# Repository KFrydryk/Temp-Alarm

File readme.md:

# Temperature Sensor with timer and Alarm

It's a home project - gift for a girlfriend. The device can measure temperature using DS18B20 sensor on a probe, show real time measurements on LCD display and set off alarm when needed. It uses barebones Atmega328 chip powered by 3 AA batteries. It can work in 4 modes.

# Work Modes
Temp | Timer | Result
-------|-------|-------
Not Set | Not Set | Temperature is printed in real time, timer counts from 0 upwards, no alarm is set
Not Set | Set | Temperature is printed in real time, timer counts down to 0, alarm when timer reaches 0
Set | Not Set | Temperature is printed in real time, timer counts from 0 upwards, alarm is set off when set temperature is reached
Set | Set | Temperature is printed in real time, timer shows set value and starts counting down when set temp is reached. Alarm is set off whem timer reaches 0

# Schematics
All schematics should be uploaded in [Eagle_files folder](https://github.com/KFrydryk/Temp-Alarm/tree/master/Eagle_files)

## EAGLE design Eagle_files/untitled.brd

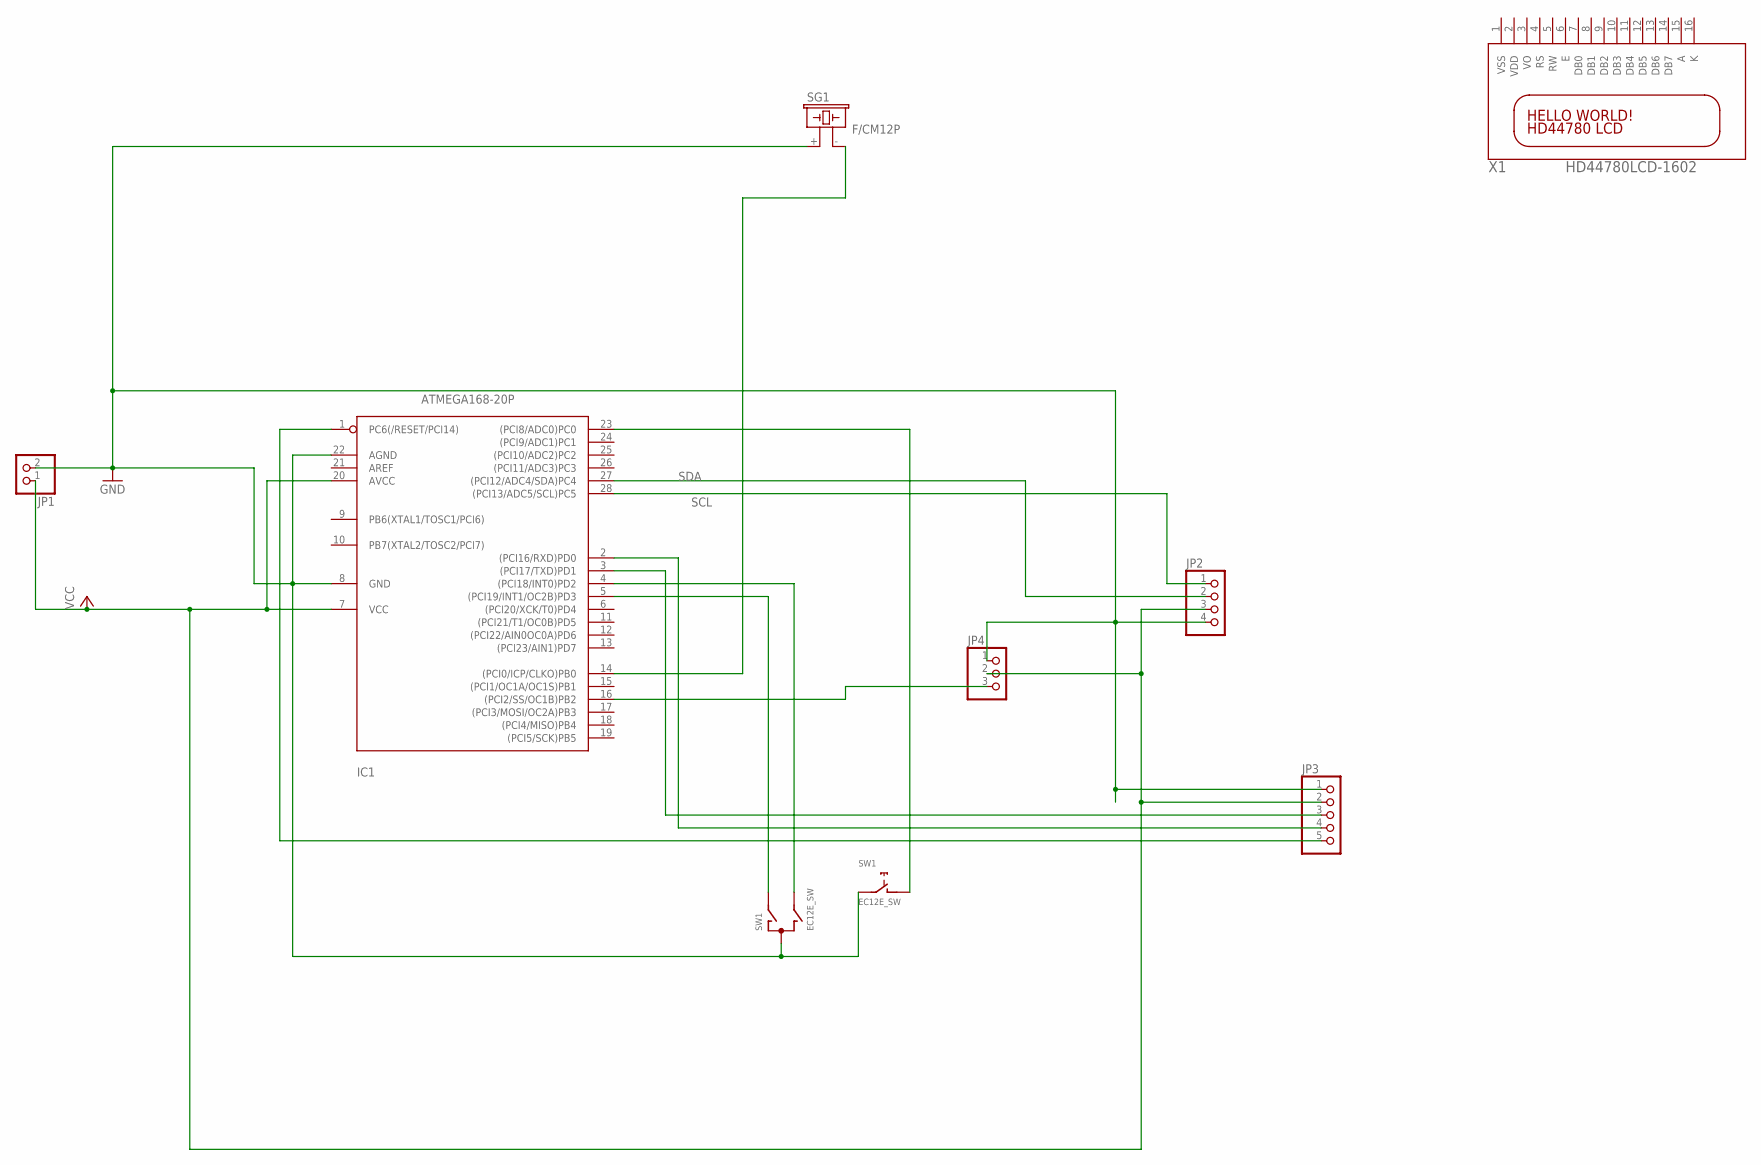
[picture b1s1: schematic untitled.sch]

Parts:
IC1: ATMEGA168-20P; DIL28-3
JP1: PINHD-1X2; 1X02
JP2: PINHD-1X4; 1X04
JP3: PINHD-1X5; 1X05
JP4: PINHD-1X3; 1X03
SG1: F/CM12P
SW1: EC12E_SW; ALPS_EC12E_SW
X1: HD44780LCD-1602; LCD1602

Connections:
GND: IC1.8 (GND), IC1.22 (AGND), JP1.2, JP2.4, JP3.1, JP4.1, SG1.+ (1), SW1.C, SW1.E (2)
unnamed: IC1.3 ((PCI17/TXD)PD1), JP3.3
unnamed: IC1.23 ((PCI8/ADC0)PC0), SW1.D (1)
unnamed: IC1.4 ((PCI18/INT0)PD2), SW1.B
unnamed: IC1.5 ((PCI19/INT1/OC2B)PD3), SW1.A
unnamed: IC1.2 ((PCI16/RXD)PD0), JP3.4
unnamed: IC1.14 ((PCI0/ICP/CLKO)PB0), SG1.- (2)
unnamed: IC1.1 (PC6(/RESET/PCI14)), JP3.5
unnamed: IC1.16 ((PCI2/SS/OC1B)PB2), JP4.3
SCL: IC1.28 ((PCI13/ADC5/SCL)PC5), JP2.1
SDA: IC1.27 ((PCI12/ADC4/SDA)PC4), JP2.2
VCC: IC1.7 (VCC), IC1.20 (AVCC), JP1.1, JP2.3, JP3.2, JP4.2

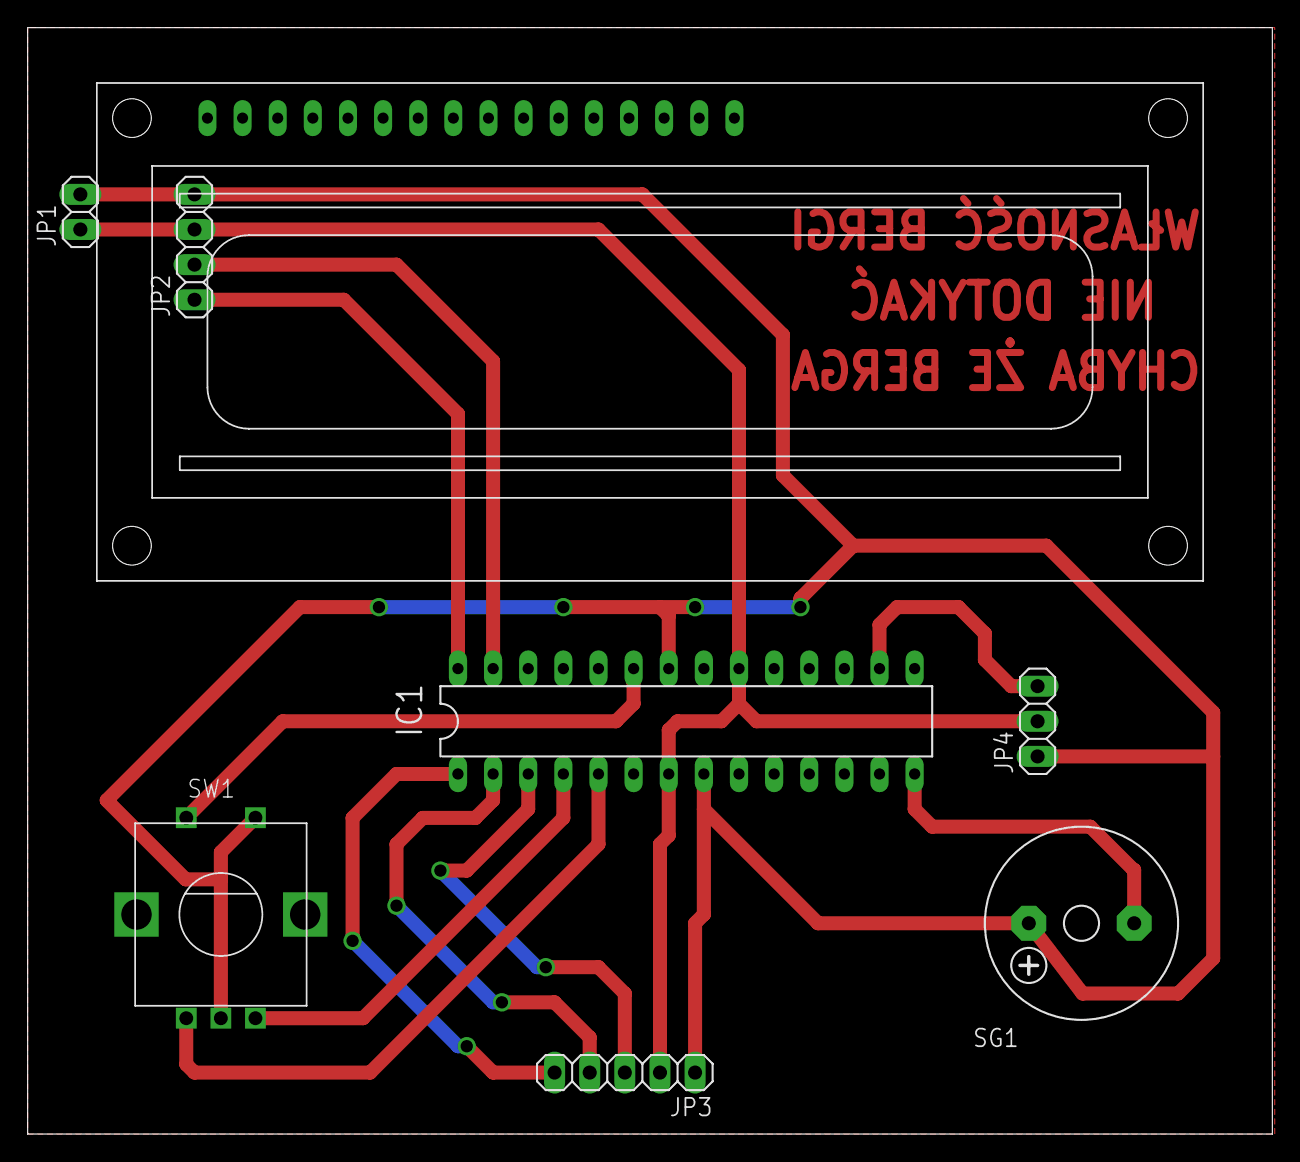
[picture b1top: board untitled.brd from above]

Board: 2 copper layers, 90.0 x 80.0 mm, 8 parts (0 on the bottom side), 12 nets.

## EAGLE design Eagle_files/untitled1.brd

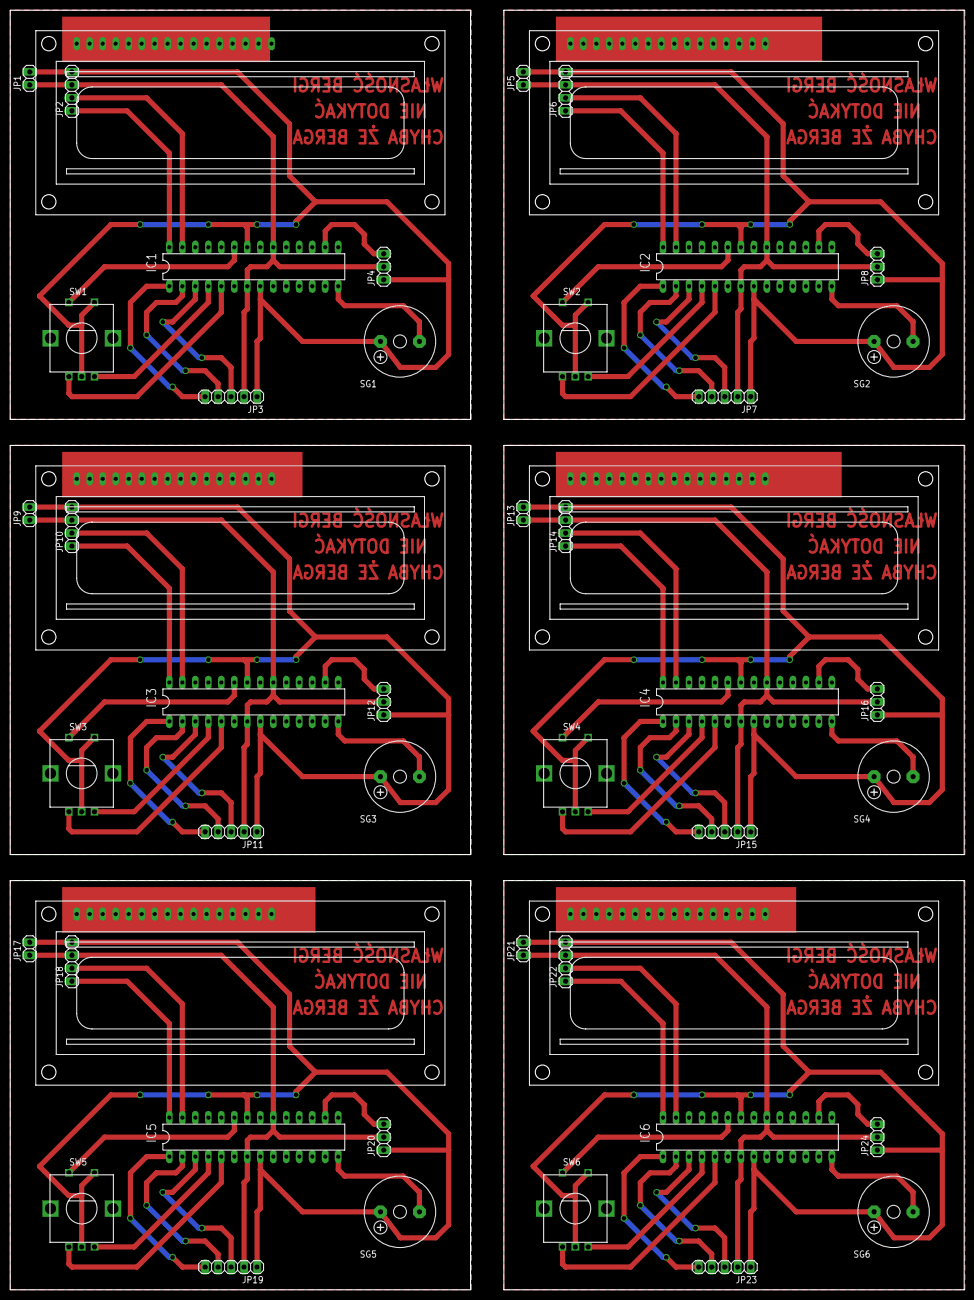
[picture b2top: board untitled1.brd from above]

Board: 2 copper layers, 186.5 x 250.2 mm, 48 parts (0 on the bottom side), 72 nets.

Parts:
IC1, IC2, IC3, IC4, IC5, IC6: ATMEGA168-20P; DIL28-3
JP1, JP5, JP9, JP13, JP17, JP21: 1X02
JP2, JP6, JP10, JP14, JP18, JP22: 1X04
JP3, JP7, JP11, JP15, JP19, JP23: 1X05
JP4, JP8, JP12, JP16, JP20, JP24: 1X03
SG1, SG2, SG3, SG4, SG5, SG6: F/CM12P
SW1, SW2, SW3, SW4, SW5, SW6: EC12E_SW; ALPS_EC12E_SW
X1, X2, X3, X4, X5, X6: HD44780LCD-1602; LCD1602

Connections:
GND: IC1.8, IC1.22, JP1.2, JP2.4, JP3.1, JP4.1, SG1.+, SW1.C, SW1.E
GND1: IC2.8, IC2.22, JP5.2, JP6.4, JP7.1, JP8.1, SG2.+, SW2.C, SW2.E
GND2: IC3.8, IC3.22, JP9.2, JP10.4, JP11.1, JP12.1, SG3.+, SW3.C, SW3.E
GND3: IC4.8, IC4.22, JP13.2, JP14.4, JP15.1, JP16.1, SG4.+, SW4.C, SW4.E
GND4: IC5.8, IC5.22, JP17.2, JP18.4, JP19.1, JP20.1, SG5.+, SW5.C, SW5.E
GND5: IC6.8, IC6.22, JP21.2, JP22.4, JP23.1, JP24.1, SG6.+, SW6.C, SW6.E
unnamed: IC1.3, JP3.3
unnamed: IC1.23, SW1.D
unnamed: IC1.4, SW1.B
unnamed: IC1.5, SW1.A
unnamed: IC1.2, JP3.4
unnamed: IC1.14, SG1.-
unnamed: IC1.1, JP3.5
unnamed: IC2.23, SW2.D
unnamed: IC1.16, JP4.3
unnamed: IC2.4, SW2.B
unnamed: IC2.5, SW2.A
unnamed: IC2.16, JP8.3
unnamed: IC2.14, SG2.-
unnamed: IC2.3, JP7.3
unnamed: IC2.2, JP7.4
unnamed: IC2.1, JP7.5
unnamed: IC3.23, SW3.D
unnamed: IC3.4, SW3.B
unnamed: IC3.5, SW3.A
unnamed: IC3.16, JP12.3
unnamed: IC3.14, SG3.-
unnamed: IC3.3, JP11.3
unnamed: IC3.2, JP11.4
unnamed: IC3.1, JP11.5
unnamed: IC4.23, SW4.D
unnamed: IC4.4, SW4.B
unnamed: IC4.5, SW4.A
unnamed: IC4.16, JP16.3
unnamed: IC4.14, SG4.-
unnamed: IC4.3, JP15.3
unnamed: IC4.2, JP15.4
unnamed: IC4.1, JP15.5
unnamed: IC5.23, SW5.D
unnamed: IC5.4, SW5.B
unnamed: IC5.5, SW5.A
unnamed: IC5.16, JP20.3
unnamed: IC5.14, SG5.-
unnamed: IC5.3, JP19.3
unnamed: IC5.2, JP19.4
unnamed: IC5.1, JP19.5
unnamed: IC6.23, SW6.D
unnamed: IC6.4, SW6.B
unnamed: IC6.5, SW6.A
unnamed: IC6.16, JP24.3
unnamed: IC6.14, SG6.-
unnamed: IC6.3, JP23.3
unnamed: IC6.2, JP23.4
unnamed: IC6.1, JP23.5
SCL: IC1.28, JP2.1
SCL1: IC2.28, JP6.1
SCL2: IC3.28, JP10.1
SCL3: IC4.28, JP14.1
SCL4: IC5.28, JP18.1
SCL5: IC6.28, JP22.1
SDA: IC1.27, JP2.2
SDA1: IC2.27, JP6.2
SDA2: IC3.27, JP10.2
SDA3: IC4.27, JP14.2
SDA4: IC5.27, JP18.2
SDA5: IC6.27, JP22.2
VCC: IC1.7, IC1.20, JP1.1, JP2.3, JP3.2, JP4.2
VCC1: IC2.7, IC2.20, JP5.1, JP6.3, JP7.2, JP8.2
VCC2: IC3.7, IC3.20, JP9.1, JP10.3, JP11.2, JP12.2
VCC3: IC4.7, IC4.20, JP13.1, JP14.3, JP15.2, JP16.2
VCC4: IC5.7, IC5.20, JP17.1, JP18.3, JP19.2, JP20.2
VCC5: IC6.7, IC6.20, JP21.1, JP22.3, JP23.2, JP24.2

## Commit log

2020-05-04 first and last commit - it's just a backup
